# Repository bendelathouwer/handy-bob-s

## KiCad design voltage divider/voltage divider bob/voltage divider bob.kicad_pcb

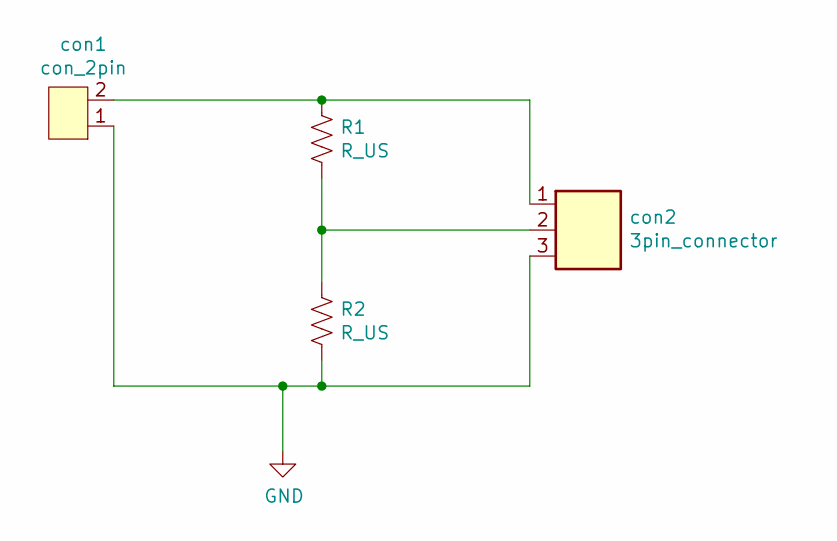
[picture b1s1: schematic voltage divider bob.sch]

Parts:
R1, R2: R_US; 0603
con1: con_2pin; 2pin_screw
con2: 3pin_connector; PinHeader_1x03_P1.27mm_Vertical

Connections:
GND: R2.2, con1.1, con2.3
unnamed: R1.1, con1.2, con2.1
unnamed: R1.2, R2.1, con2.2

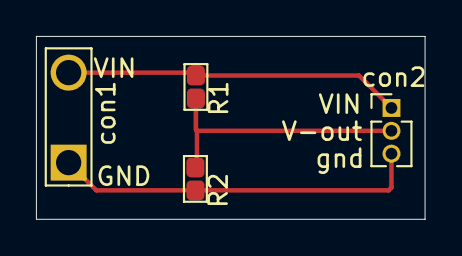
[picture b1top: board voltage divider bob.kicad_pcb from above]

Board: 2 copper layers, 21.6 x 10.2 mm, 4 parts (0 on the bottom side), 3 nets.

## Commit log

2020-12-17 voltage divider bob
    voltage divider bob toegevoegd
2020-12-17 silkscreen
    silkscreen toegevoegd
2020-12-17 gerber
    gerbers opgeschoond
